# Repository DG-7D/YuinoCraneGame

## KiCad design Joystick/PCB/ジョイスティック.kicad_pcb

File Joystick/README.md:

# Joystick 
- ESP32
  - 5V: 5V
  - GND: GND
  - to Motor Driver
    - RX(to TX): 16
    - TX(to RX): 17
  - to Joystick
    - X-axis: 27
    - Y-axis: 26
    - Button: 25
    - Button LED: 12

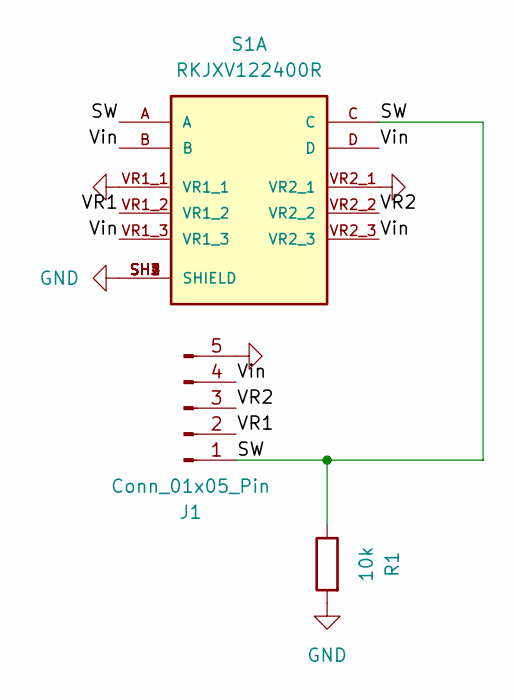
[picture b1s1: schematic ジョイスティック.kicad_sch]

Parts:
J1: Conn_01x05_Pin; PinHeader_1x05_P2.54mm_Horizontal
R1: 10k; R_0603_1608Metric
S1: RKJXV122400R; SW_RKJXV122400R; PARTREV N/A

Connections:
/SW: J1.1, R1.1, S1.A, S1.C
/VR1: J1.2, S1.VR1_2
/VR2: J1.3, S1.VR2_2
/Vin: J1.4, S1.B, S1.D, S1.VR1_3, S1.VR2_3
GND: J1.5, R1.2, S1.SH1 (SHIELD), S1.SH2 (SHIELD), S1.SH3 (SHIELD), S1.SH4 (SHIELD), S1.VR1_1, S1.VR2_1

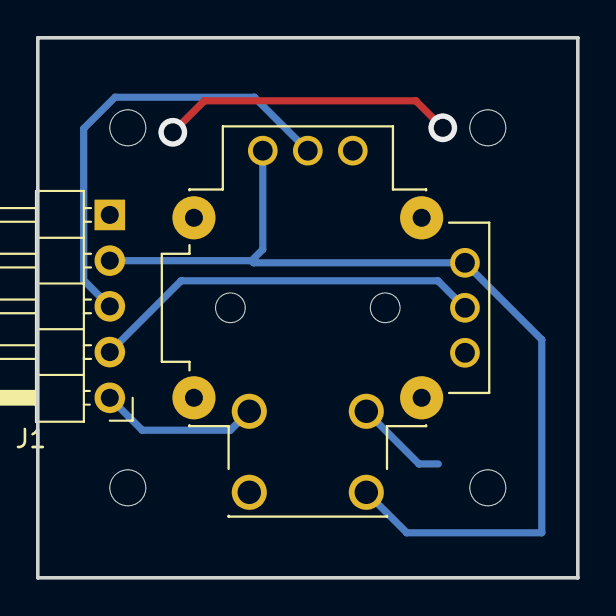
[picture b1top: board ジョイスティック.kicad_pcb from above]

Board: 2 copper layers, 30.0 x 30.0 mm, 3 parts (1 on the bottom side), 5 nets.

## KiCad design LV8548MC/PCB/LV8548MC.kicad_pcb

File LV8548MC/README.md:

# LV8548MC

LV8548MCを2つまとめただけの基板です。

## ピン配置

### 入力端子 (右上)

左から0-7

### 出力端子 (右)

下から7-0

### 電源入力端子 (左下)

左から
- GND
- VCC

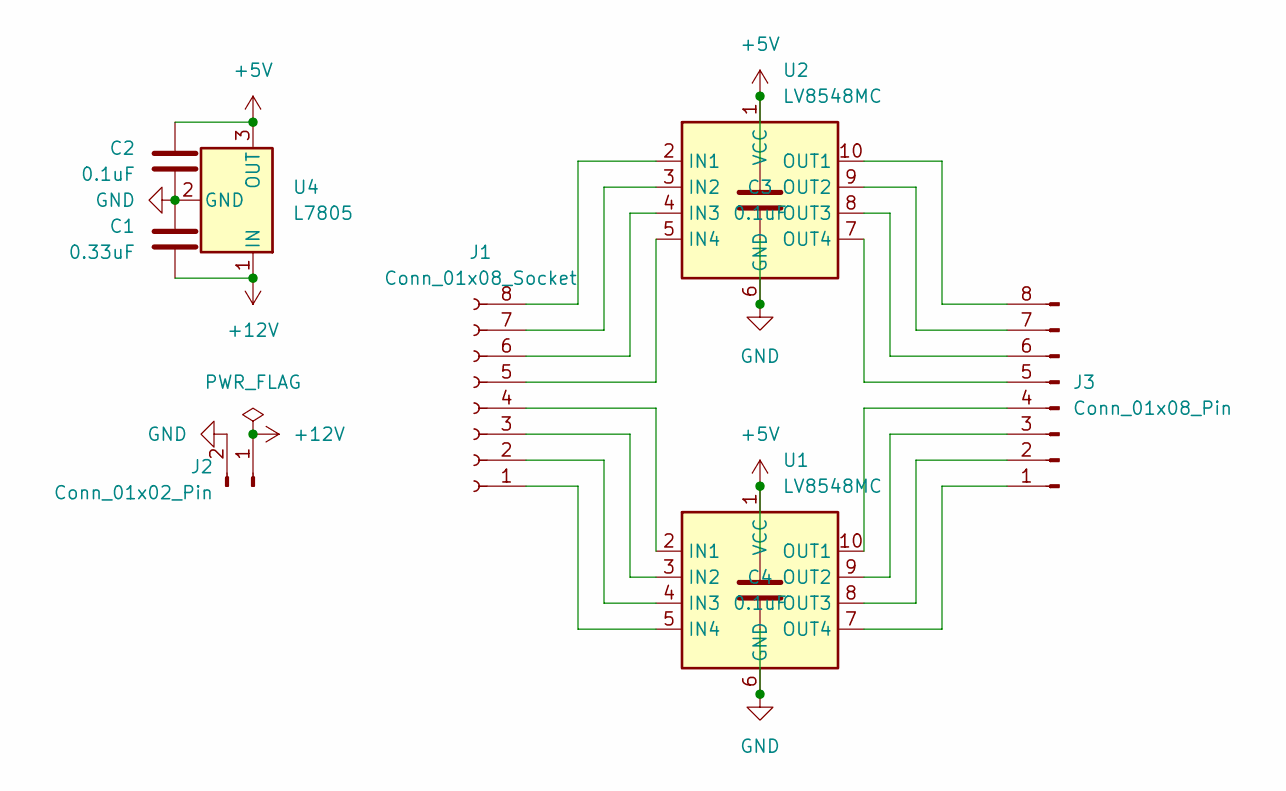
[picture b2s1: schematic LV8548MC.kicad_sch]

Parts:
C1: 0.33uF; C_0603_1608Metric_Pad1.08x0.95mm_HandSolder
C2, C3, C4: 0.1uF; C_0603_1608Metric_Pad1.08x0.95mm_HandSolder
J1: Conn_01x08_Socket; PinSocket_1x08_P2.54mm_Horizontal
J2: Conn_01x02_Pin; PinHeader_1x02_P2.54mm_Horizontal
J3: Conn_01x08_Pin; PinHeader_1x08_P2.54mm_Horizontal
U1, U2: LV8548MC; SOIC-10_3.9x4.9mm_P1mm
U4: L7805; TO-220-3_Horizontal_TabDown

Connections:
+5V: C2.1, C3.1, C4.1, U1.1 (VCC), U2.1 (VCC), U4.3 (OUT)
+12V: C1.1, J2.1, U4.1 (IN)
GND: C1.2, C2.2, C3.2, C4.2, J2.2, U1.6 (GND), U2.6 (GND), U4.2 (GND)
unnamed: J1.1, U1.5 (IN4)
unnamed: J1.2, U1.4 (IN3)
unnamed: J1.3, U1.3 (IN2)
unnamed: J1.4, U1.2 (IN1)
unnamed: J1.5, U2.5 (IN4)
unnamed: J1.6, U2.4 (IN3)
unnamed: J1.7, U2.3 (IN2)
unnamed: J1.8, U2.2 (IN1)
unnamed: J3.1, U1.7 (OUT4)
unnamed: J3.2, U1.8 (OUT3)
unnamed: J3.3, U1.9 (OUT2)
unnamed: J3.4, U1.10 (OUT1)
unnamed: J3.5, U2.7 (OUT4)
unnamed: J3.6, U2.8 (OUT3)
unnamed: J3.7, U2.9 (OUT2)
unnamed: J3.8, U2.10 (OUT1)

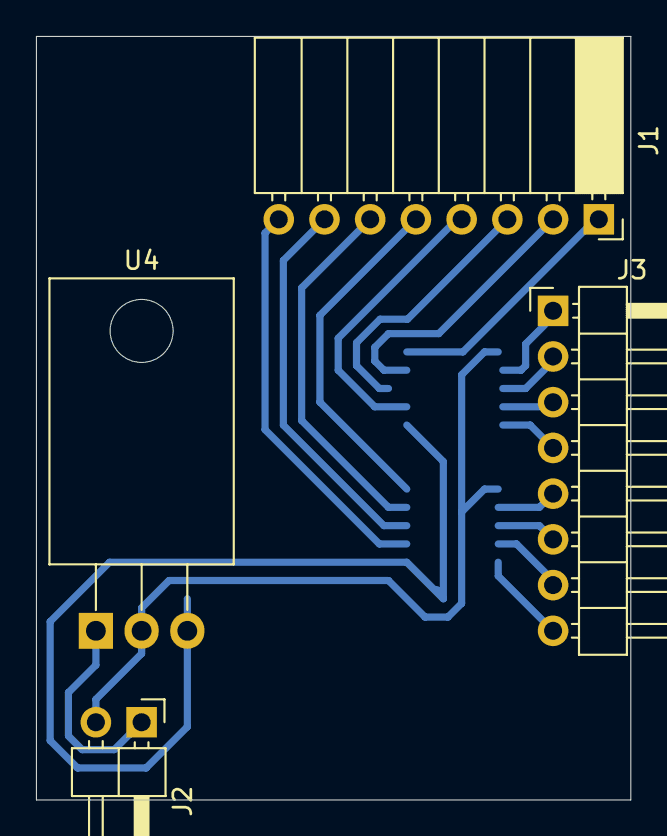
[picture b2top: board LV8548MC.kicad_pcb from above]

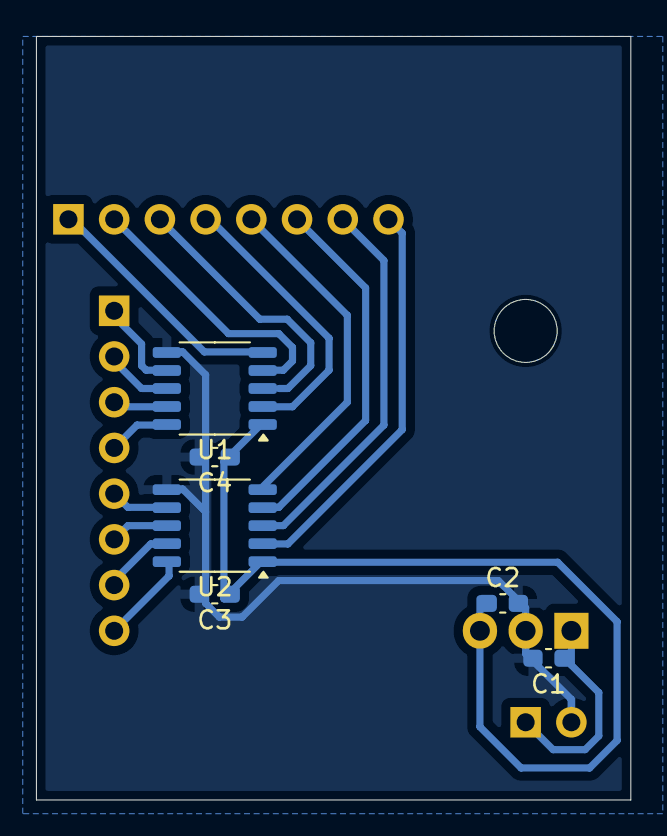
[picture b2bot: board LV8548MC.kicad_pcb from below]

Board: 2 copper layers, 33.0 x 42.4 mm, 10 parts (6 on the bottom side), 19 nets.

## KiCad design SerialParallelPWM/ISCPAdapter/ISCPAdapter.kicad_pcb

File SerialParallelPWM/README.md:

# PWM出力シリアルパラレル変換器

UARTで受信したビット列の各ビットに対応するピンから予め設定されたデューティー比のPWM信号を出力します。通常のシリアルパラレル変換器と異なりクロックが不要かつPWM出力ができます。

## ピン配置

### シリアル端子 (左上)

左から
- RESET
- TX
- RX

### パラレル出力端子 (中央上)

左から0-7

### 5V入力端子 (右上)

左から
- 5V
- GND

### 電源入力端子 (左下)

左から
- GND
- VCC

## 使い方

1バイト(8bit)のデータを受信すると、それぞれのビットが出力に対応します。

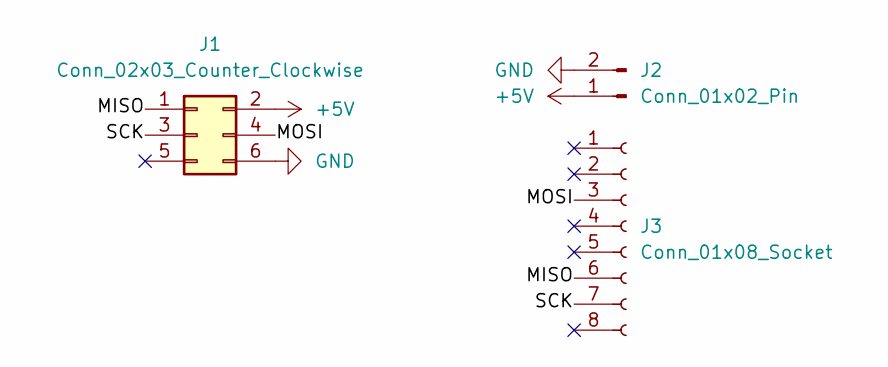
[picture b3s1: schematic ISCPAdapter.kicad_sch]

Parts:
J1: Conn_02x03_Counter_Clockwise; PinSocket_2x03_P2.54mm_Vertical
J2: Conn_01x02_Pin; PinHeader_1x02_P2.54mm_Horizontal
J3: Conn_01x08_Socket; PinSocket_1x08_P2.54mm_Horizontal

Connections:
+5V: J1.2, J2.1
/MISO: J1.1, J3.6
/MOSI: J1.4, J3.3
/SCK: J1.3, J3.7
GND: J1.6, J2.2

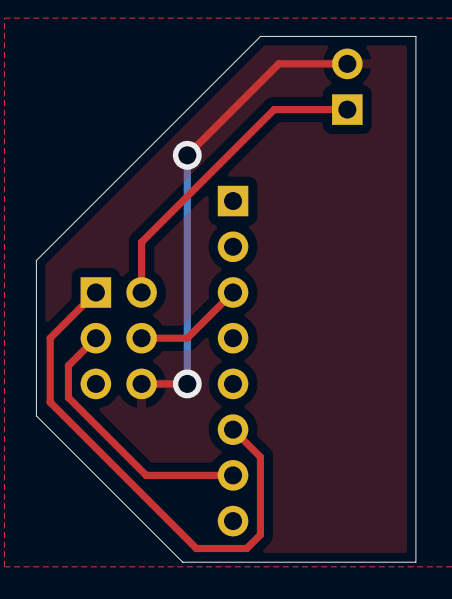
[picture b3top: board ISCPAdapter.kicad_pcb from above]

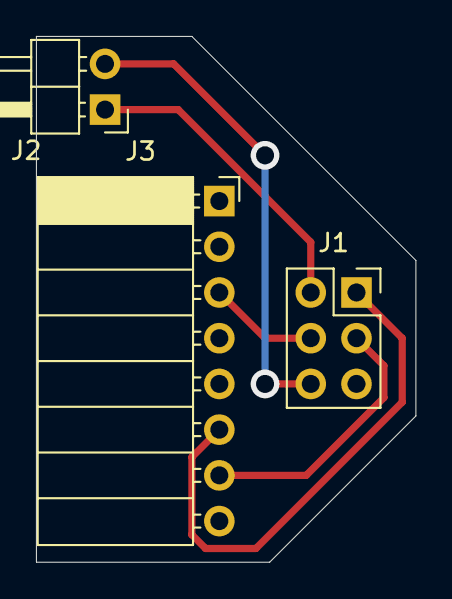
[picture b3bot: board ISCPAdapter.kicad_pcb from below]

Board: 2 copper layers, 21.1 x 29.2 mm, 3 parts (3 on the bottom side), 5 nets.

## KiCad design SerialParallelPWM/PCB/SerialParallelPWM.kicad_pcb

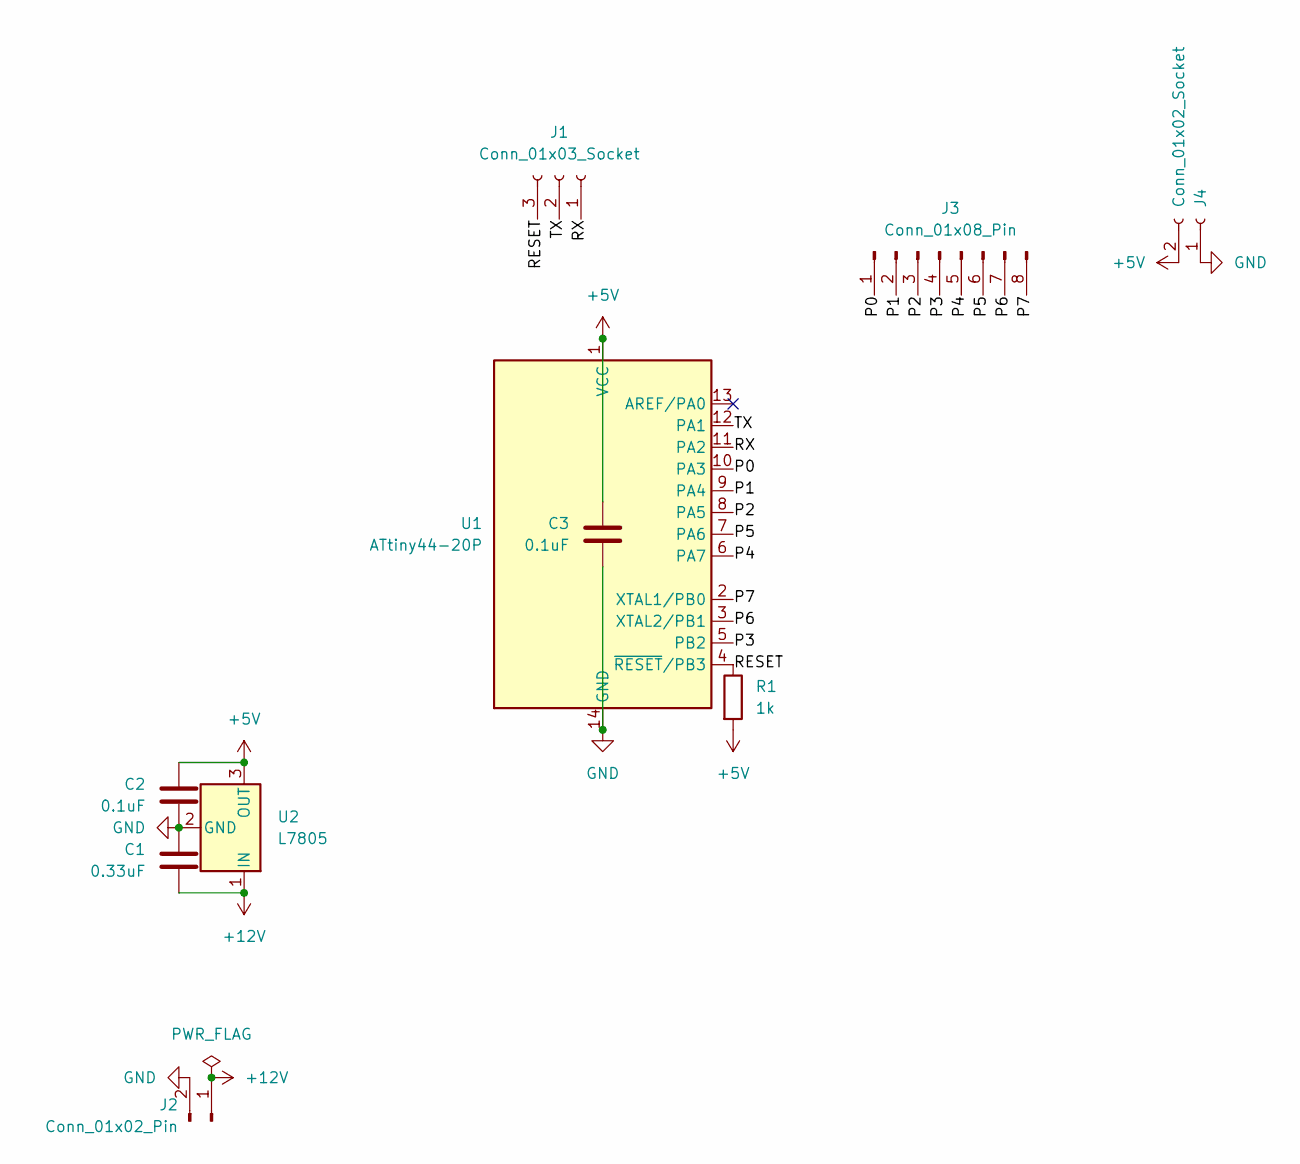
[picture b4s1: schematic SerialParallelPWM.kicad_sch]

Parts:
C1: 0.33uF; C_0603_1608Metric_Pad1.08x0.95mm_HandSolder
C2, C3: 0.1uF; C_0603_1608Metric_Pad1.08x0.95mm_HandSolder
J1: Conn_01x03_Socket; PinSocket_1x03_P2.54mm_Horizontal
J2: Conn_01x02_Pin; PinHeader_1x02_P2.54mm_Horizontal
J3: Conn_01x08_Pin; PinHeader_1x08_P2.54mm_Horizontal
J4: Conn_01x02_Socket; PinSocket_1x02_P2.54mm_Horizontal
R1: 1k; R_0603_1608Metric_Pad0.98x0.95mm_HandSolder
U1: ATtiny44-20P; DIP-14_W7.62mm_Socket
U2: L7805; TO-220-3_Horizontal_TabDown

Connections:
+5V: C2.1, C3.1, J4.2, R1.2, U1.1 (VCC), U2.3 (OUT)
+12V: C1.2, J2.1, U2.1 (IN)
/P0: J3.1, U1.10 (PA3)
/P1: J3.2, U1.9 (PA4)
/P2: J3.3, U1.8 (PA5)
/P3: J3.4, U1.5 (PB2)
/P4: J3.5, U1.6 (PA7)
/P5: J3.6, U1.7 (PA6)
/P6: J3.7, U1.3 (XTAL2/PB1)
/P7: J3.8, U1.2 (XTAL1/PB0)
/RESET: J1.3, R1.1, U1.4 (~RESET/PB3)
/RX: J1.1, U1.11 (PA2)
/TX: J1.2, U1.12 (PA1)
GND: C1.1, C2.2, C3.2, J2.2, J4.1, U1.14 (GND), U2.2 (GND)

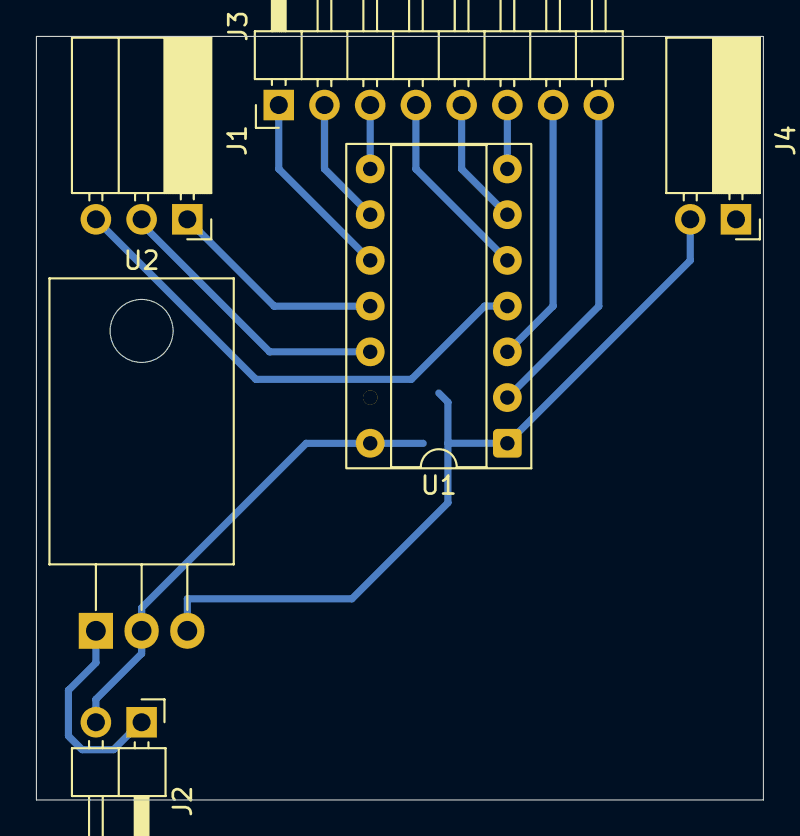
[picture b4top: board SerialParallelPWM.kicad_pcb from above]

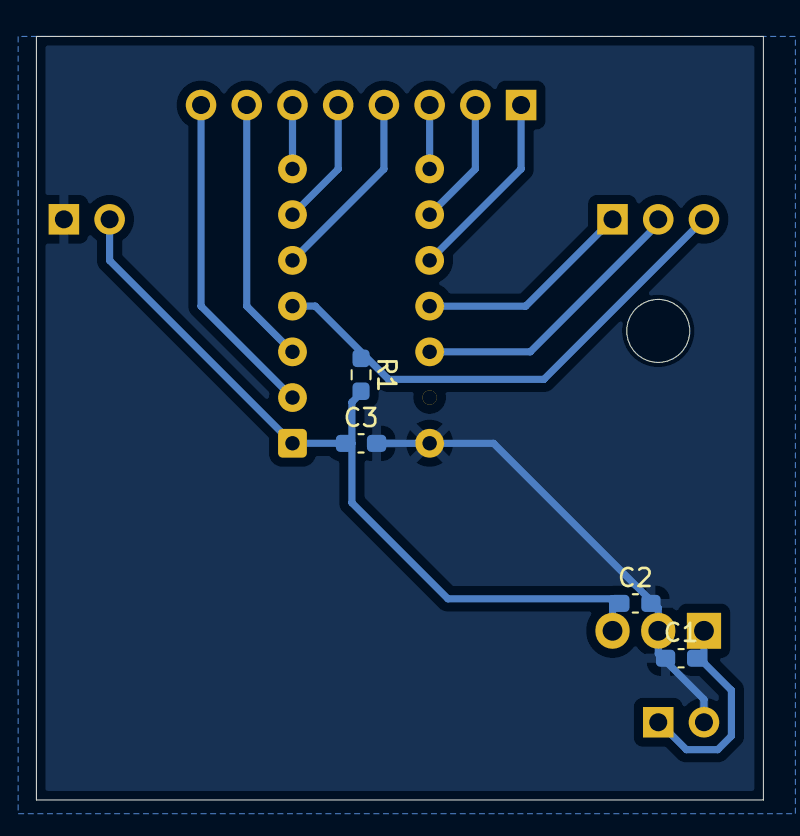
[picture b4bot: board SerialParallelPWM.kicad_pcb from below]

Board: 2 copper layers, 40.4 x 42.4 mm, 10 parts (4 on the bottom side), 14 nets.

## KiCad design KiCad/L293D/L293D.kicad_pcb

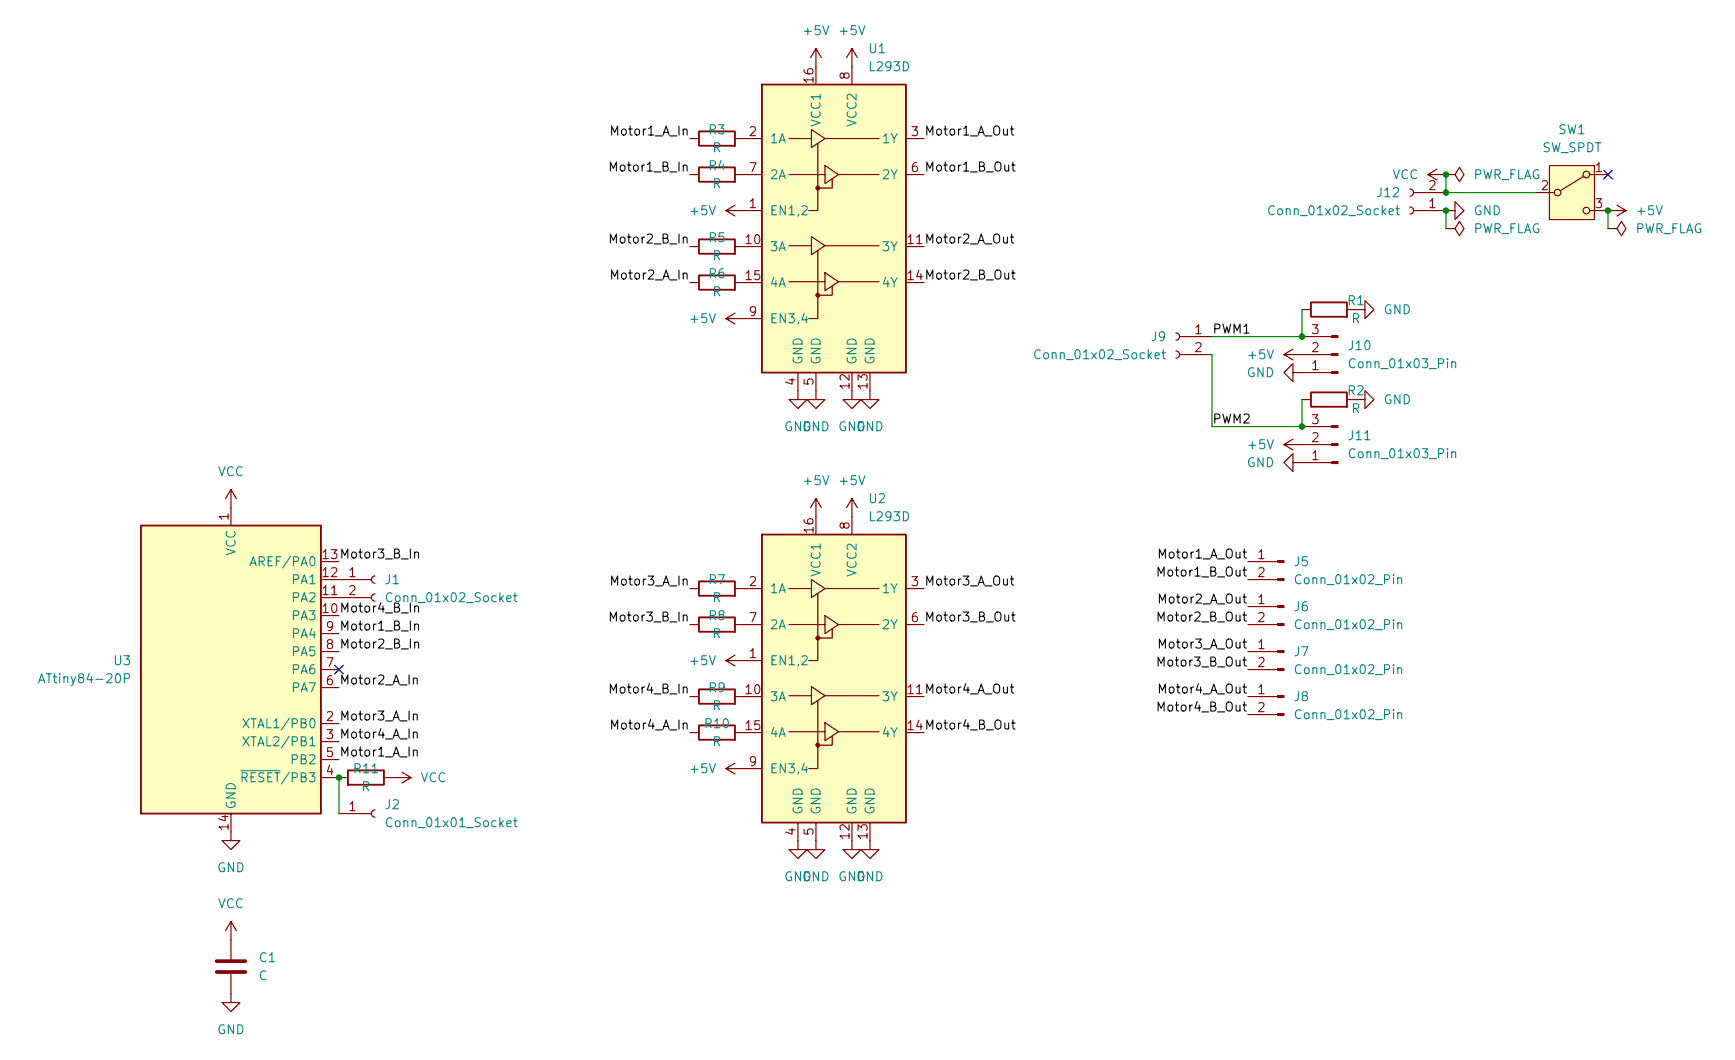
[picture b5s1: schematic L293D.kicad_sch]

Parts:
C1: C; C_0603_1608Metric_Pad1.08x0.95mm_HandSolder
J1, J9, J12: Conn_01x02_Socket; PinSocket_1x02_P2.54mm_Vertical
J2: Conn_01x01_Socket; PinSocket_1x01_P2.54mm_Vertical
J5, J6, J7, J8: Conn_01x02_Pin; PinHeader_1x02_P2.54mm_Vertical
J10, J11: Conn_01x03_Pin; PinHeader_1x03_P2.54mm_Vertical
R1, R2, R3, R4, R5, R6, R7, R8, R9, R10, R11: R; R_0603_1608Metric_Pad0.98x0.95mm_HandSolder
SW1: SW_SPDT; PinHeader_1x03_P2.54mm_Vertical
U1, U2: L293D; DIP-16_W7.62mm_Socket
U3: ATtiny84-20P; DIP-14_W7.62mm_Socket

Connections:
+5V: J10.2, J11.2, SW1.3 (C), U1.1 (EN1,2), U1.8 (VCC2), U1.9 (EN3,4), U1.16 (VCC1), U2.1 (EN1,2), U2.8 (VCC2), U2.9 (EN3,4), U2.16 (VCC1)
/Motor1_A_In: R3.1, U3.5 (PB2)
/Motor1_A_Out: J5.1, U1.3 (1Y)
/Motor1_B_In: R4.1, U3.9 (PA4)
/Motor1_B_Out: J5.2, U1.6 (2Y)
/Motor2_A_In: R6.1, U3.6 (PA7)
/Motor2_A_Out: J6.1, U1.11 (3Y)
/Motor2_B_In: R5.1, U3.8 (PA5)
/Motor2_B_Out: J6.2, U1.14 (4Y)
/Motor3_A_In: R7.1, U3.2 (XTAL1/PB0)
/Motor3_A_Out: J7.1, U2.3 (1Y)
/Motor3_B_In: R8.1, U3.13 (AREF/PA0)
/Motor3_B_Out: J7.2, U2.6 (2Y)
/Motor4_A_In: R10.1, U3.3 (XTAL2/PB1)
/Motor4_A_Out: J8.1, U2.11 (3Y)
/Motor4_B_In: R9.1, U3.10 (PA3)
/Motor4_B_Out: J8.2, U2.14 (4Y)
/PWM1: J9.1, J10.3, R1.1
/PWM2: J9.2, J11.3, R2.1
GND: C1.2, J10.1, J11.1, J12.1, R1.2, R2.2, U1.4 (GND), U1.5 (GND), U1.12 (GND), U1.13 (GND), U2.4 (GND), U2.5 (GND), U2.12 (GND), U2.13 (GND), U3.14 (GND)
unnamed: J1.1, U3.12 (PA1)
unnamed: J1.2, U3.11 (PA2)
unnamed: J2.1, R11.2, U3.4 (~RESET/PB3)
unnamed: R3.2, U1.2 (1A)
unnamed: R4.2, U1.7 (2A)
unnamed: R5.2, U1.10 (3A)
unnamed: R6.2, U1.15 (4A)
unnamed: R7.2, U2.2 (1A)
unnamed: R8.2, U2.7 (2A)
unnamed: R9.2, U2.10 (3A)
unnamed: R10.2, U2.15 (4A)
VCC: C1.1, J12.2, R11.1, SW1.2 (B), U3.1 (VCC)

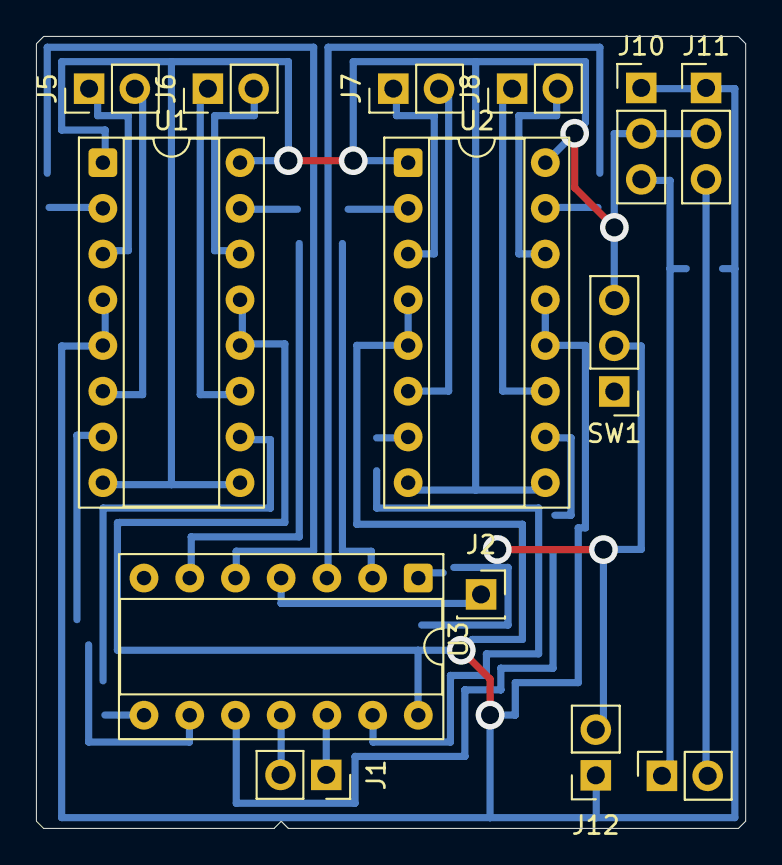
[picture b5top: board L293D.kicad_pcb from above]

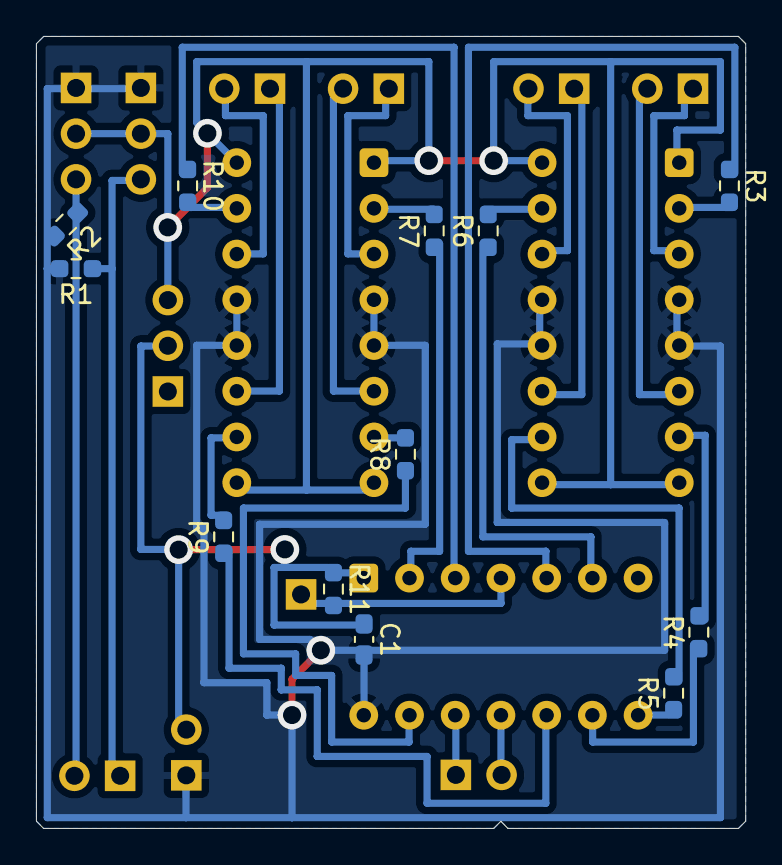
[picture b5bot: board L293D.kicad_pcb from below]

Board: 2 copper layers, 39.4 x 44.0 mm, 26 parts (12 on the bottom side), 32 nets.

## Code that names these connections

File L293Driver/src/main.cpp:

#include <Arduino.h>

constexpr uint8_t motorCount = 4;
constexpr uint8_t outputCount = 2 * motorCount;

constexpr uint8_t portAvailable[2] = {0b11111001, 0b00000111}; // PA2(RXD), PA1(TXD), PB3(RESET)には触れない
constexpr byte portMappingArray[outputCount][2] = {
    {0, 1 << 2}, // PB2
    {1 << 4, 0}, // PA4
    {1 << 7, 0}, // PA7
    {1 << 5, 0}, // PA5
    {0, 1 << 0}, // PB0
    {1 << 0, 0}, // PA0
    {0, 1 << 1}, // PB1
    {1 << 3, 0}  // PA3
};

constexpr uint8_t pulseWidthArray[outputCount] = {31, 31,
                                                  63, 63,
                                                  127, 127,
                                                  255, 255}; // TCNT0(0-255)と比較 2^n - 1のほうが速い

uint8_t portEnabled[2] = {0, 0};

void setup() {
    Serial.begin(9600);
    DDRA |= portAvailable[0];
    DDRB |= portAvailable[1];
}

void loop() {
    while (Serial.available() > 0) {
        uint8_t motorStateFlag = Serial.read();
        portEnabled[0] = 0;
        portEnabled[1] = 0;
        for (uint8_t i = 0; i < outputCount; i++) {
            if (bitRead(motorStateFlag, i)) {
                portEnabled[0] |= portMappingArray[i][0];
                portEnabled[1] |= portMappingArray[i][1];
            }
        }
        Serial.write(motorStateFlag);
    }

    uint8_t portPWM[2] = {0, 0};
    for (uint8_t i = 0; i < outputCount; i++) {
        if (TCNT0 <= pulseWidthArray[i]) {
            portPWM[0] |= portMappingArray[i][0];
            portPWM[1] |= portMappingArray[i][1];
        }
    }

    PORTA = (PORTA & ~portAvailable[0]) | (portEnabled[0] & portPWM[0]);
    PORTB = (PORTB & ~portAvailable[1]) | (portEnabled[1] & portPWM[1]);
}

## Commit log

2024-11-22 いにしゃるこみっと
2024-11-22 サーボピン要変更
2024-11-22 操作中出力を追加
2024-11-22 間違ったリミットスイッチを参照していたのを修正
2024-11-22 原点復帰でまっすぐ戻るようになったかもしれない
2024-11-22 Y軸の制御の処理を修正、不要な定数を削除
2024-11-23 ピン配置修正、ゼロ除算修正
2024-11-23 操作終了時に暴走するのを修正
2024-11-23 原点復帰しないのを修正
2024-11-23 原点復帰の挙動を単純に戻した
2024-11-23 ピン配置ドキュメント追加
2024-11-23 README修正
2024-11-23 最初の入力を待てていなかったのを修正
2024-11-23 delayを削除、信号の判定式を統一
2024-11-23 各動作のタイミングをいいかんじにした
2024-11-24 XY軸の個別設定に対応
2024-11-24 下げる時間と上げる時間を変えられるようにした
2024-11-24 確率を調整
2024-11-24 巻上時間調整
2024-11-24 Z軸の時間を調整
2024-11-24 Z軸リミットスイッチ対応
2024-11-24 Z軸巻上時指定時間であきらめるよう変更
2024-11-24 制御プログラムをサブディレクトリに移動
2025-01-25 びみょい
2025-01-26 動きそう(有効期限設定してない)
2025-01-27 パラメータ調整
2025-01-27 リミットスイッチを見るようにした
2025-01-27 止めるときに0にするようにした
2025-03-21 L293DのCAD
2025-03-23 L293Dの基板をつくった
2025-03-23 L293D基板用ぷろぐらむ
2025-03-23 ビアをでかくした
2025-03-23 PWMの周波数上げても耐えそう
2025-03-25 ピンによってパルス幅を変えられるようにした
2025-03-31 ATtiny44にした、内蔵クロックの設定をした
2025-03-31 シリアルしばくやつつくった
2025-04-01 設定追加したら動いた
2025-04-01 ATtinyが返事するようにした
2025-04-01 Revert "設定追加したら動いた"
    This reverts commit 6cbb29fd8f0ff04b36fe2659b9c5731ed7a8a2af.
2025-04-01 gitignoreを追加
2025-04-04 ブートローダを書き込めるようにした
2025-04-04 wip シールドを介してGNDがつながってる
2025-04-05 L293D基板を更新 出力に直列抵抗を追加 パスコンを追加 リセット入力を追加
2025-04-07 microsやめた
2025-04-07 uno破壊
2025-04-07 ピン出力もレジスタをしばくようにした
2025-04-07 ピン修正
2025-04-08 多分全部つながった
2025-04-13 optiboot経由での書き込みに対応
2025-04-16 バカの配線を破壊
2025-04-16 add gitigonore
2025-04-16 新しいコントローラー
2025-04-19 もろもろの場所変更
2025-04-20 ヒューズビット修正
2025-04-22 とりあえず部品置いた
2025-04-22 LV8548MC基板
2025-04-22 パラレル変換基板
2025-04-22 README
2025-04-22 ISCPアダプタ
2025-05-16 ピン配置を新基板に合わせた
2025-11-20 ジョイスティックをセンターに配置
2025-11-20 joystick制御 v1
2025-11-20 一応動く ピンの修正とかバグの修正とか
2025-11-20 ESP32Servoライブラリの追加
2025-11-20 モータ速度変更
2025-11-22 WIP 遊星ギヤ対応版
2025-11-22 純正版platformを明示
2025-11-22 ジョイスティック: プルアップに変更
2025-11-22 ジョイスティック: いろいろ
2025-11-22 もろもろ修正
2025-11-23 古いものを削除
2025-12-03 掲示用PDF
